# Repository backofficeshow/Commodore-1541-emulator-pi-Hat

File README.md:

# Commodore-1541-emulator-pi-Hat
Raspberry Pi Hat for Steve White's Excellent software emulated 1541

Feel free to use this design for your own personal use. If you want to use it in your commercial design please contact me first, this is a community supported design and to play fair its nice to be asked!

Steve White's excellent project:
https://cbm-pi1541.firebaseapp.com/

The video stream about this design:
https://youtu.be/9ZHAoGowLNE

The video stream about the build:
https://www.youtube.com/watch?v=_NtLqHfJCsg

Backofficeshow links:
https://www.youtube.com/backofficeshow
https://www.backofficeshow.com

Please feel free to ping me on twitter: @backofficeshow
or be a real superstar and consider buying me a coffee via Patreon: https://www.patreon.com/BackofficeShow

TODO:

Replace level shifting components with integrated circuit: http://www.ti.com/lit/ds/symlink/txb0108.pdf

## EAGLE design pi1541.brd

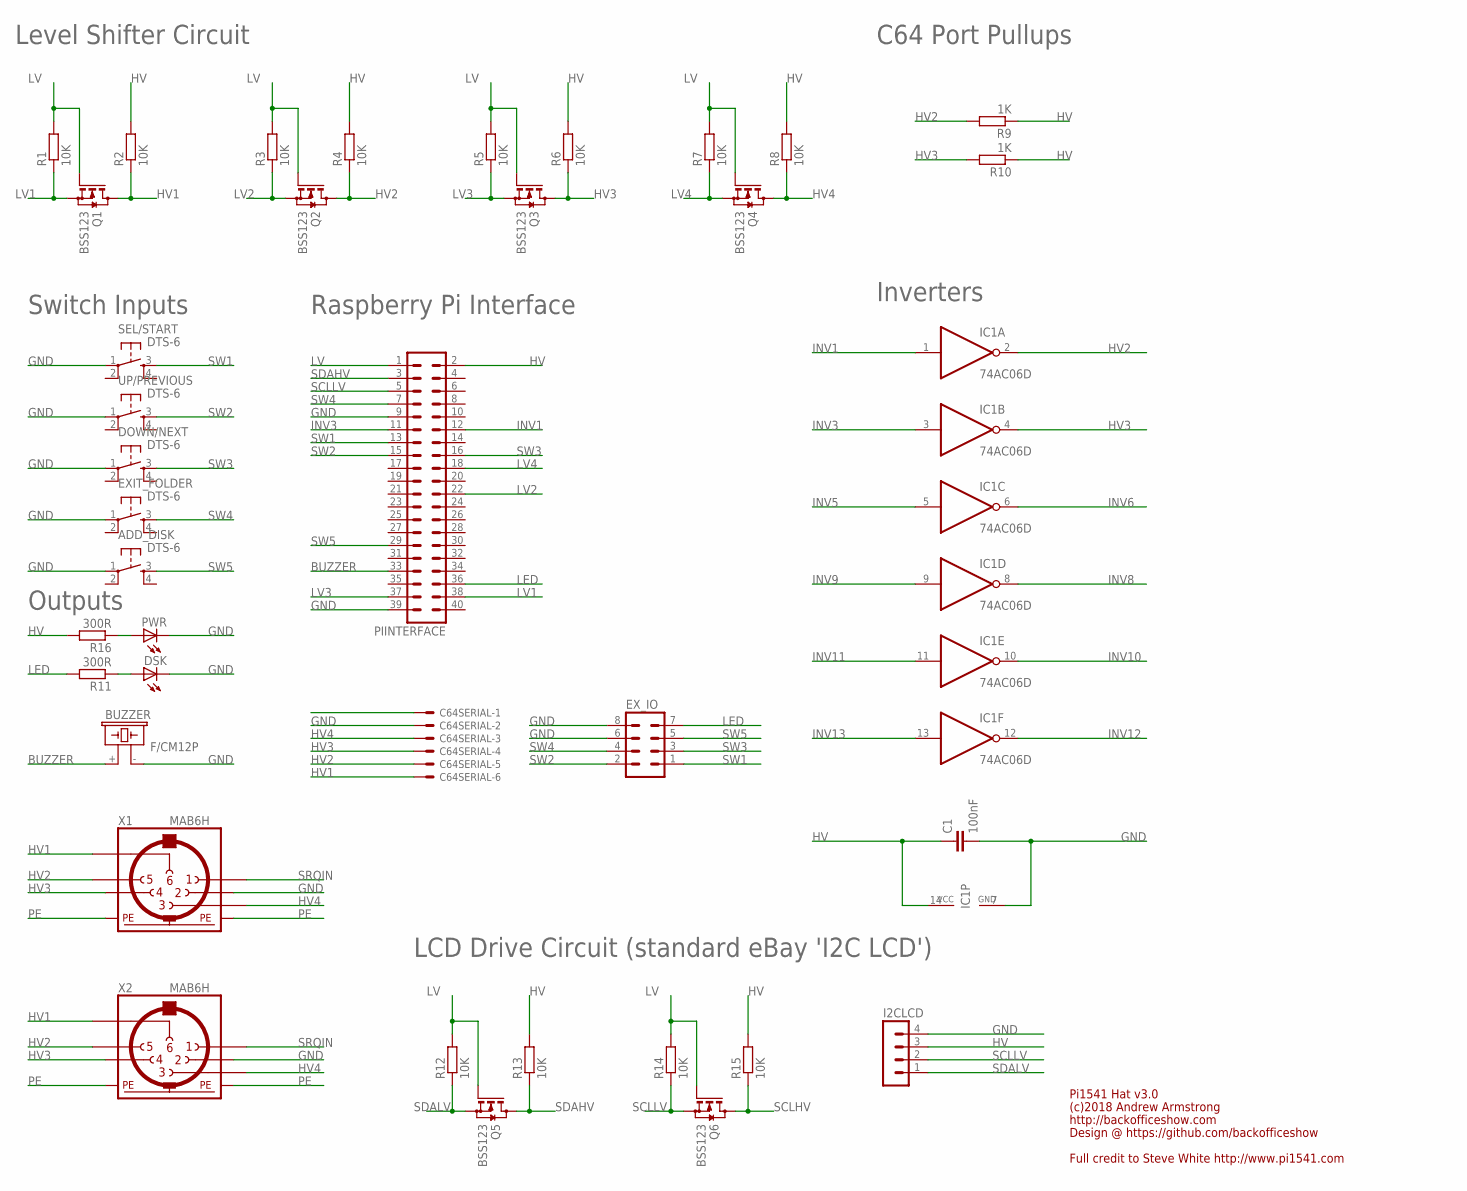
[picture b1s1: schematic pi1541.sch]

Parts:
ADD_DISK: DTS-6
BUZZER: F/CM12P
C1: 100nF; C0805
C64SERIAL: 22-23-2061
DOWN/NEXT: DTS-6
DSK: LEDCHIPLED_0805; CHIPLED_0805
EXIT_FOLDER: DTS-6
EX_IO: MA04-2
I2CLCD: MA04-1
IC1: 74AC06D; SO14
PIINTERFACE: MA20-2
PWR: LEDCHIPLED_0805; CHIPLED_0805
Q1, Q2, Q3, Q4, Q5, Q6: BSS123; SOT23
R1, R2, R3, R4, R5, R6, R7, R8, R12, R13, R14, R15: 10K; R0805
R9, R10: 1K; R0805
R11, R16: 300R; R0805
SEL/START: DTS-6
UP/PREVIOUS: DTS-6
X1, X2: MAB6H

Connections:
BUZZER: BUZZER.+ (1), PIINTERFACE.33
GND: ADD_DISK.1, BUZZER.- (2), C1.2, C64SERIAL.2, DOWN/NEXT.1, DSK.C, EXIT_FOLDER.1, EX_IO.6, EX_IO.8, I2CLCD.4, IC1.7 (GND), PIINTERFACE.9, PIINTERFACE.39, PWR.C, SEL/START.1, UP/PREVIOUS.1, X1.2, X2.2
HV: C1.1, I2CLCD.3, IC1.14 (VCC), PIINTERFACE.2, R2.2, R4.2, R6.2, R8.2, R9.1, R10.1, R13.2, R15.2, R16.2
HV1: C64SERIAL.6, Q1.3 (D), R2.1, X1.6, X2.6
HV2: C64SERIAL.5, IC1.2 (O), Q2.3 (D), R4.1, R9.2, X1.5, X2.5
HV3: C64SERIAL.4, IC1.4 (O), Q3.3 (D), R6.1, R10.2, X1.4, X2.4
HV4: C64SERIAL.3, Q4.3 (D), R8.1, X1.3, X2.3
INV1: IC1.1 (I), PIINTERFACE.12
INV3: IC1.3 (I), PIINTERFACE.11
INV5: IC1.5 (I)
INV6: IC1.6 (O)
INV8: IC1.8 (O)
INV9: IC1.9 (I)
INV10: IC1.10 (O)
INV11: IC1.11 (I)
INV12: IC1.12 (O)
INV13: IC1.13 (I)
LED: EX_IO.7, PIINTERFACE.36, R11.2
LV: PIINTERFACE.1, Q1.1 (G), Q2.1 (G), Q3.1 (G), Q4.1 (G), Q5.1 (G), Q6.1 (G), R1.2, R3.2, R5.2, R7.2, R12.2, R14.2
LV1: PIINTERFACE.38, Q1.2 (S), R1.1
LV2: PIINTERFACE.22, Q2.2 (S), R3.1
LV3: PIINTERFACE.37, Q3.2 (S), R5.1
LV4: PIINTERFACE.18, Q4.2 (S), R7.1
unnamed: DSK.A, R11.1
unnamed: PWR.A, R16.1
PE: X1.PE, X1.PE@ (PE), X2.PE, X2.PE@ (PE)
SCLHV: Q6.3 (D), R15.1
SCLLV: I2CLCD.2, PIINTERFACE.5, Q6.2 (S), R14.1
SDAHV: PIINTERFACE.3, Q5.3 (D), R13.1
SDALV: I2CLCD.1, Q5.2 (S), R12.1
SRQIN: X1.1, X2.1
SW1: EX_IO.1, PIINTERFACE.13, SEL/START.3
SW2: EX_IO.2, PIINTERFACE.15, UP/PREVIOUS.3
SW3: DOWN/NEXT.3, EX_IO.3, PIINTERFACE.16
SW4: EXIT_FOLDER.3, EX_IO.4, PIINTERFACE.7
SW5: ADD_DISK.3, EX_IO.5, PIINTERFACE.29

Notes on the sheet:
Level Shifter Circuit
Inverters
C64 Port Pullups
Raspberry Pi Interface
Switch Inputs
LCD Drive Circuit (standard eBay 'I2C LCD')
Full credit to Steve White http://www.pi1541.com
Pi1541 Hat v3.0
(c)2018 Andrew Armstrong
http://backofficeshow.com
Design @ https://github.com/backofficeshow
Outputs

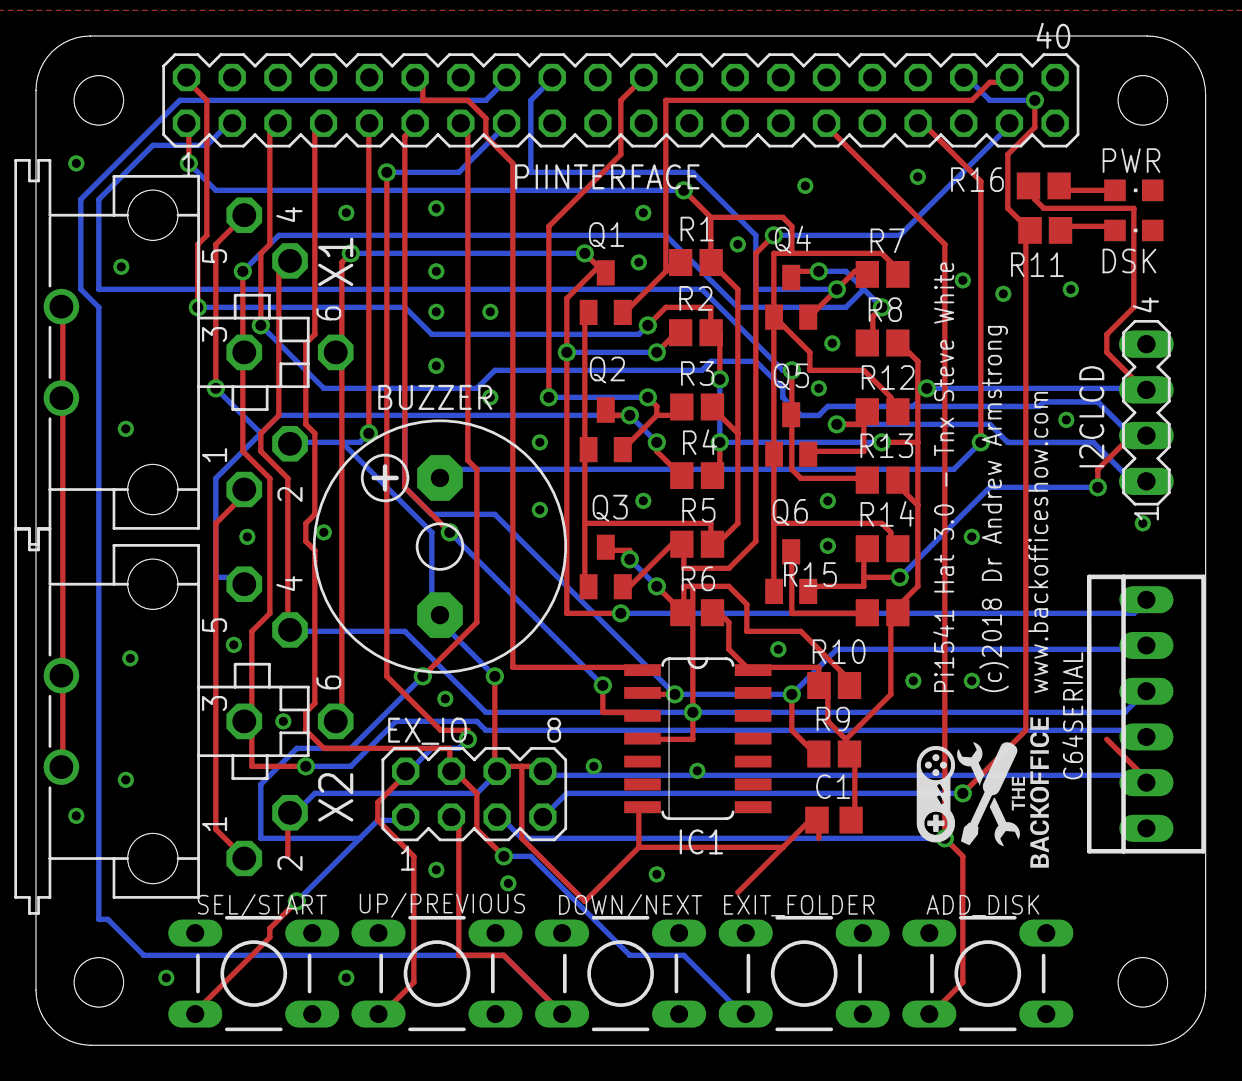
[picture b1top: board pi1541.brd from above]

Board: 2 copper layers, 65.0 x 56.1 mm, 38 parts (0 on the bottom side), 28 nets.

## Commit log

2018-05-28 Updated Footprint for Alpha Print
    Ready to have prototype made now and see what happens!
    Mainly footprint adjusted to Pi3 spacing
2018-05-28 Bitmap to show layout
2018-07-08 Version 2
    Now with additional serial interface ports for those wishing to use a DIN interconnect. Everything else remains the same electrically as tested already by Rob Taylor.
2018-07-08 Screenshot of the V2 PCB
2018-07-08 Image of the V1 Board
    Kindly Manufactured by Rob Taylor for testing.
2018-07-08 Corrected via tenting
2018-08-20 Bill of materials export
2018-08-22 Updates
    Added Power LED
    Modified OLED Header for more common boards available
    Modified Tactile switches to through hole variety to ease construction
2018-08-22 Not Needed
